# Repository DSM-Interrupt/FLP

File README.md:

# 구성

project FLP의 기기의 회로도, PCB, FW 코드 등이 담긴 파일입니다.
호스트 기기의 프레임 워크는 ESP-IDF를 이용하였고 Espressif ide를 이용하여서 CMAKE 형식의 프로젝트로 제작되었습니다.
터미널 기기의 프레임 워크는 STMCUBE를 이용하였습니다. 
host 기기의 같은경우 MCU는 ESP32-WROOM-32E를 이용하였으며 terminal기기의 경우 STM32F103C8T6을 사용하였습니다.

## 세부내용
### Hardware
- 433MHz 대역 통신을 위해 SX1278 모듈 기반의 안테나 매칭을 포함한 LoRa RF 공통 회로 설계
- MCP73831(Li-Po 충전) 및 AP2112K-3.3(LDO)을 사용하여 USB-C/배터리 입력을 받는 3.3V 전원 시스템 공통 회로 구성
- CP2104 USB-to-UART 브릿지 IC와 USB-C 커넥터를 사용한 PC 시리얼 통신 및 펌웨어 다운로드 공통 회로 구현
- L86-M33 GPS 모듈을 탑재하여 위치 정보 수집을 위한 공통 회로 및 안테나 인터페이스 설계
- Host(ESP32) 보드에 펌웨어의 효율적인 디버깅을 위한 JTAG 인터페이스 회로 추가 설계

### Firmware
- Host(ESP32) 펌웨어는 C 언어와 ESP-IDF(FreeRTOS)를 기반으로, Terminal(STM32F103) 펌웨어는 C 언어와 HAL 라이브러리를 기반으로 개발하여 LoRa 통신 시스템을 구축
- Terminal은 UART2로 GPS 모듈의 NMEA 센텐스를 파싱하며, 5초 주기 또는 '호출'/'위험' 버튼 입력 시 고유 ID, GPS 좌표, Target ID, 위험 상태를 "ID,Lat,Lon,TargetID,Danger" 형식의 문자열 패킷으로 LoRa 전송
- Host는 SPI를 통해 이 LoRa 패킷을 수신, split_lora_response 함수로 파싱하여 Target ID를 확인하고, TerminalDevice 구조체 배열로 관리되는 단말기 목록의 최신 GPS 좌표와 위험 상태를 갱신
- Host는 Wi-Fi(AP+STA 모드)로 인터넷에 연결하며, WSS 클라이언트를 통해 원격 서버로 모든 단말기 정보와 자체 GPS 수신 정보를 통합하여 주기적으로 JSON 전송
- Wi-Fi AP 모드에서 Captive Portal 기능을 포함한 웹 서버를 구동하여 사용자에게 Wi-Fi 연결 정보 및 AP 정보 설정 페이지를 제공하며, 이 설정값들과 등록된 단말기 ID 목록은 NVS에 영속 저장
- 특정 GPIO 버튼(CTRL + FIND_HOST) 조합을 통해 10초간 '단말기 등록 모드'로 진입하며, 이 동안 수신된 "REG,<ID>,<TARGET_ID>" 형식의 LoRa 등록 요청 패킷을 처리하여 새로운 단말기를 시스템에 추가하고 NVS에 저장

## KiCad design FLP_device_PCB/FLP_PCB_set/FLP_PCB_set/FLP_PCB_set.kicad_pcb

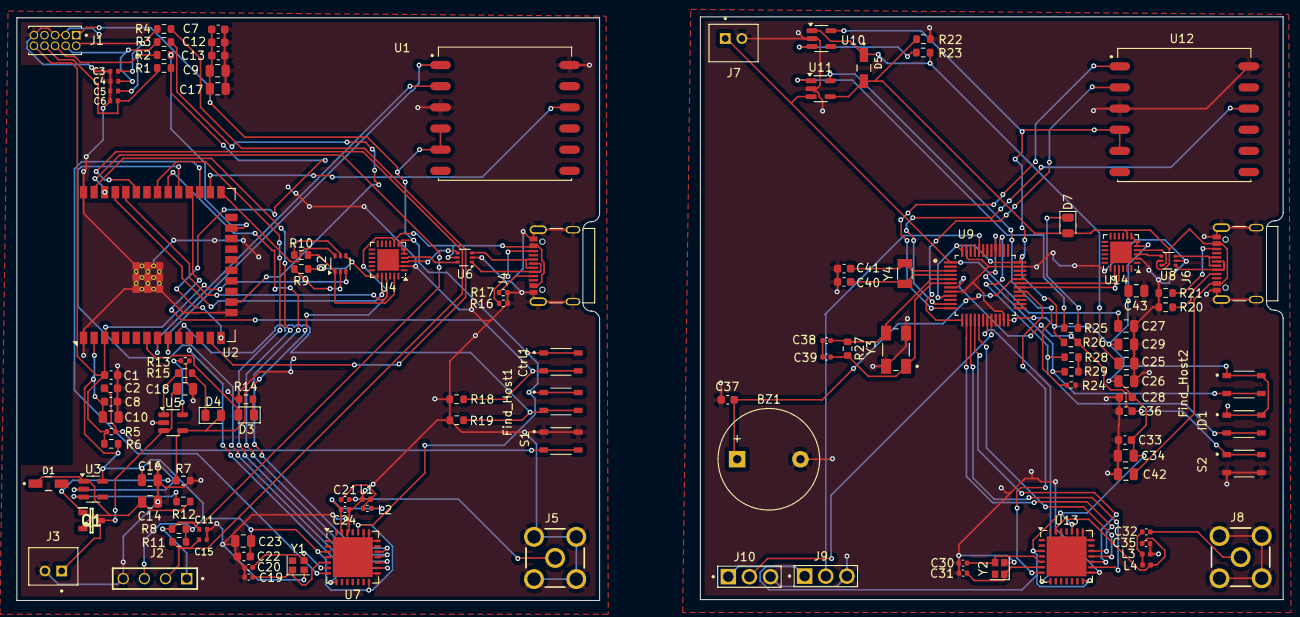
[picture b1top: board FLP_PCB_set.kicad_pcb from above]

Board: 2 copper layers, 152.1 x 70.1 mm, 118 parts (0 on the bottom side), 93 nets.

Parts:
BZ1: FQ 010; Buzzer_12x9.5RM7.6
C1, C7, C8, C28, C37: 1uF; C_0603_1608Metric
C2, C12, C22, C33, C36: 0.1uF; C_0603_1608Metric
C3, C4, C5, C6, C11, C15: PESD0402-140; RESC1005X35N
C9, C10, C14, C16, C18, C23, C25, C26, C27, C29, C34, C42: 22uF; C_0805_2012Metric
C13: 4.7uF; C_0603_1608Metric
C17, C43: 10uF; C_0805_2012Metric
C19, C20, C30, C31: 12pF; C_0402_1005Metric
C21, C32: 15pF; C_0402_1005Metric
C24, C35: 3.3pF; C_0402_1005Metric
C38, C39: 20pF; C_0402_1005Metric
C40, C41: 18pF; C_0603_1608Metric
Ctrl1: SKRPABE010; SW_SKRPABE010
D1, D5: MBR120VLSFT1G; DIOM3616X98N
D3, D4, D7: 150080GS75000; LED_0805_2012Metric
Find_Host1, Find_Host2: SKRPABE010; SW_SKRPABE010
ID1: SKRPABE010; SW_SKRPABE010
J1: GRPB052VWVN-RC; SULLINS_GRPB052VWVN-RC
J2: OLED; SAMTEC_HTSW-104-20-TM-S
J3, J7: B2B-PH-K-S; JST_B2B-PH-K-S
J4, J6: 12402012E212A; AMPHENOL_12402012E212A
J5, J8: SMA-J-P-X-ST-TH1; SAMTEC_SMA-J-P-X-ST-TH1
J9, J10: 61300311121; WURTH_61300311121
L1, L3: 47nH; L_0402_1005Metric
L2: 18nH; C_0402_1005Metric
L4: 18nH; L_0402_1005Metric
Q1: DMG3415UQ-7; SOT96P240X110-3N
Q2: UMH3N; SOT-363_SC-70-6
R1, R2, R3, R4: 100R; R_0603_1608Metric
R5: 22R; R_0402_1005Metric
R6, R9, R10, R18, R19, R26, R28, R29: 10K; R_0603_1608Metric
R7, R12, R22, R23: 100K; R_0603_1608Metric
R8, R11: 2.2K; R_0603_1608Metric
R13, R24: 2K; R_0402_1005Metric
R14, R15, R25: 1K; R_0603_1608Metric
R16, R17: 5.1K; R_0402_1005Metric
R20, R21: 5.1K; R_0603_1608Metric
R27: 1M; R_0603_1608Metric
S1, S2: SKRPABE010; SW_SKRPABE010
U1, U12: L86-M33; XCVR_L86-M33
U2: ESP32-WROOM-32E
U3, U10: AP2112K-3.3; SOT-23-5
U4, U14: CP2104; QFN-24-1EP_4x4mm_P0.5mm_EP2.6x2.6mm
U5, U11: MCP73831-2-OT; SOT-23-5
U6, U8: USBLC6-2P6; SOT-666
U7, U13: SX1278; QFN-28-1EP_6x6mm_P0.65mm_EP4.8x4.8mm
U9: STM32F103C8T6; QFP50P900X900X160-48N
Y1, Y2: 32MHz; Crystal_SMD_2016-4Pin_2.0x1.6mm
Y3: ABM3B-8.000MHZ-B2-T; XTAL_ABM3B-8.000MHZ-B2-T
Y4: 32.768kHz; Crystal_SMD_3215-2Pin_3.2x1.5mm

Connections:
/FLP_host/3.3V_OUT: C7.1, C8.1, C9.1, C10.1, C12.1, C13.1, C16.1, C17.1, C22.1, C23.2, Ctrl1.1, Ctrl1.2, Find_Host1.1, Find_Host1.2, J1.1, J2.03, R6.2, R8.2, R11.2, U1.4 (VCC), U1.5 (V_BCKP), U2.2 (VDD), U3.5 (VOUT), U4.5 (VIO), U4.6 (VDD), U4.7 (REGIN), U7.3 (VBAT_ANA), U7.14 (VBAT_DIG), U7.24 (VBAT_RF)
/FLP_host/5v_USB_OUT: D1.2, D4.2 (A), J4.A4_B9 (VBUS), J4.B4_A9 (VBUS), Q1.1 (G), R7.1, U4.8 (VBUS), U5.4 (V_{DD}), U6.5 (VBUS)
/FLP_host/Ctrl: Ctrl1.3, Ctrl1.4, R18.1, U2.28 (IO17)
/FLP_host/DIO0(IRQ): U2.11 (IO26), U7.8 (DIO0)
/FLP_host/DTR: Q2.1 (E1), R10.1, U4.23 (~DTR)
/FLP_host/Find_Host: Find_Host1.3, Find_Host1.4, R19.1, U2.10 (IO25)
/FLP_host/GPS_Reset: U1.10 (~RESET), U2.26 (IO4)
/FLP_host/GPS_Rx: U1.1 (RXD1), U2.9 (IO33)
/FLP_host/GPS_TX: U1.2 (TXD1), U2.8 (IO32)
/FLP_host/I2C_SCL: C11.1, J2.01, R8.1, U2.36 (IO22)
/FLP_host/I2C_SDL: C15.1, J2.02, R11.1, U2.33 (IO21)
/FLP_host/IO0: Q2.6 (C1), U2.25 (IO0)
/FLP_host/MISO: U2.31 (IO19), U7.17 (MISO)
/FLP_host/MOSI: U2.37 (IO23), U7.18 (MOSI)
/FLP_host/MTCK: R3.1, U2.16 (IO13)
/FLP_host/MTDI: R1.1, U2.14 (IO12)
/FLP_host/MTDO: R2.1, U2.23 (IO15)
/FLP_host/MTMS: R4.1, U2.13 (IO14)
/FLP_host/NSS(CS): U2.30 (IO18), U7.19 (NSS)
/FLP_host/RESET: U2.27 (IO16), U7.7 (~RESET)
/FLP_host/RTS: Q2.4 (E2), R9.1, U4.19 (~RTS)
/FLP_host/RX: U2.34 (RXD0/IO3), U4.21 (TXD)
/FLP_host/SCK: U2.29 (IO5), U7.16 (SCK)
/FLP_host/TEST LED: D3.2 (A), U2.7 (IO35)
/FLP_host/TX: U2.35 (TXD0/IO1), U4.20 (RXD)
/FLP_host/VBAT: C18.1, J3.1, Q1.3 (D), U5.3 (V_{BAT})
/FLP_terminal/BOOT_Mode/3.3V_in: C26.1, C28.1, C29.1, C33.1, C34.2, C43.1, Find_Host2.1, Find_Host2.2, ID1.1, ID1.2, J9.1, J10.1, R26.1, U9.9 (VDDA), U9.24 (VDD), U9.36 (VDD), U9.48 (VDD), U10.5 (VOUT), U12.4 (VCC), U12.5 (V_BCKP), U13.3 (VBAT_ANA), U13.14 (VBAT_DIG), U13.24 (VBAT_RF), U14.5 (VIO), U14.6 (VDD), U14.7 (REGIN)
/FLP_terminal/BOOT_Mode/BOOT0: J9.2, U9.44 (BOOT0)
/FLP_terminal/BOOT_Mode/BOOT1: J10.2, U9.20 (PB2)
/FLP_terminal/Bat/5v_USB_OUT: C42.2, D5.2, D7.2 (A), J6.A4_B9 (VBUS), J6.B4_A9 (VBUS), R22.1, U8.5 (VBUS), U11.4 (V_{DD}), U14.8 (VBUS)
/FLP_terminal/Bat/VBAT: C27.1, J7.1, U9.1 (VBAT), U11.3 (V_{BAT})
/FLP_terminal/GPS/GPS_Reset: U9.11 (PA1), U12.10 (~RESET)
/FLP_terminal/GPS/GPS_Rx: U9.12 (PA2), U12.1 (RXD1)
/FLP_terminal/GPS/GPS_TX: U9.13 (PA3), U12.2 (TXD1)
/FLP_terminal/LoRa/DIO0(IRQ): U9.19 (PB1), U13.8 (DIO0)
/FLP_terminal/LoRa/MISO: U9.16 (PA6), U13.17 (MISO)
/FLP_terminal/LoRa/MOSI: U9.17 (PA7), U13.18 (MOSI)
/FLP_terminal/LoRa/NSS(CS): U9.14 (PA4), U13.19 (NSS)
/FLP_terminal/LoRa/RESET: U9.29 (PA8), U13.7 (~RESET)
/FLP_terminal/LoRa/SCK: U9.15 (PA5), U13.16 (SCK)
/FLP_terminal/STM32/Buzzer: BZ1.1 (+), C37.1, U9.32 (PA11)
/FLP_terminal/STM32/Find_Host: Find_Host2.3, Find_Host2.4, R29.1, U9.40 (PB4)
/FLP_terminal/STM32/ID: ID1.3, ID1.4, R28.1, U9.39 (PB3)
/FLP_terminal/STM32/OSC_IN: C38.2, R27.1, U9.5 (PD0_OSC_IN), Y3.3
/FLP_terminal/STM32/OSC_OUT: C39.2, R27.2, U9.6 (PD1_OSC_OUT), Y3.1
/FLP_terminal/STM32/PC_OSC_IN: C41.1, U9.3 (PC14-OSC32_IN), Y4.1
/FLP_terminal/STM32/PC_OSC_OUT: C40.1, U9.4 (PC15-OSC32_OUT), Y4.2
/FLP_terminal/STM32/RX: U9.31 (PA10), U14.21 (TXD)
/FLP_terminal/STM32/TX: U9.30 (PA9), U14.20 (RXD)
/FLP_terminal/UART_USB/CC_1: J6.A5 (CC1), R20.1
/FLP_terminal/UART_USB/CC_2: J6.B5 (CC2), R21.1
/FLP_terminal/UART_USB/D+: U8.4 (I/O2), U14.3 (D+)
/FLP_terminal/UART_USB/D-: U8.6 (I/O1), U14.4 (D-)
EN: C1.1, J1.10, Q2.3 (C2), R5.2, R6.1, U2.3 (EN)
GND: BZ1.2 (-), C1.2, C2.1, C3.2, C4.1, C5.1, C6.2, C7.2, C8.2, C9.2, C10.2, C11.2, C12.2, C13.2, C14.2, C15.2, C16.2, C17.2, C18.2, C19.1, C20.1, C22.2, C23.1, C24.2, C25.2, C26.2, C27.2, C28.2, C29.2, C30.1, C31.1, C33.2, C34.1, C35.2, C36.1, C37.2, C40.2, C41.2, C42.1, C43.2, J1.3, J1.5, J1.9, J2.04, J3.2, J4.A1_B12 (GND), J4.B1_A12 (GND), J4.SH1 (SHIELD), J4.SH2 (SHIELD), J4.SH3 (SHIELD), J4.SH4 (SHIELD), J5.2, J5.3, J5.4, J5.5, J6.A1_B12 (GND), J6.B1_A12 (GND), J6.SH1 (SHIELD), J6.SH2 (SHIELD), J6.SH3 (SHIELD), J6.SH4 (SHIELD), J7.2, J8.2, J8.3, J8.4, J8.5, J9.3, J10.3, L1.1, L3.1, R7.2, R13.1, R14.2, R16.1, R17.1, R18.2, R19.2, R20.2, R21.2, R22.2, R24.1, R28.2, R29.2, S1.1, S1.2, S2.3, S2.4, U1.3 (GND), U1.12 (GND), U2.1 (GND), U2.15 (GND), U2.38 (GND), U2.39 (GND), U3.2 (GND), U4.2 (GND), U4.25 (GND), U5.2 (V_{SS}), U6.2 (GND), U7.15 (GND), U7.21 (GND), U7.22 (GND), U7.23 (GND), U7.26 (GND), U7.29 (GND), U8.2 (GND), U9.8 (VSSA), U9.23 (VSS), U9.35 (VSS), U9.47 (VSS), U10.2 (GND), U11.2 (V_{SS}), U12.3 (GND), U12.12 (GND), U13.15 (GND), U13.21 (GND), U13.22 (GND), U13.23 (GND), U13.26 (GND), U13.29 (GND), U14.2 (GND), U14.25 (GND), Y3.2 (GND), Y3.4 (GND)
unnamed: C2.2, R5.1, S1.3, S1.4
unnamed: C3.1, J1.2, R4.2
unnamed: C4.2, J1.4, R3.2
unnamed: C5.2, J1.6, R2.2
unnamed: C6.1, J1.8, R1.2
unnamed: C21.1, L1.2, L2.1
unnamed: C21.2, J5.1
unnamed: C32.1, L3.2, L4.1
unnamed: C32.2, J8.1
unnamed: C38.1, C39.1
unnamed: D3.1 (K), R14.1
unnamed: D4.1 (K), R15.2
unnamed: D7.1 (K), R25.2
unnamed: J4.A5 (CC1), R17.2
unnamed: J4.B5 (CC2), R16.2
unnamed: J4.A6 (D+), J4.B6 (D+), U6.3 (I/O2)
unnamed: J4.A7 (D-), J4.B7 (D-), U6.1 (I/O1)
unnamed: J6.A6 (D+), J6.B6 (D+), U8.3 (I/O2)
unnamed: J6.A7 (D-), J6.B7 (D-), U8.1 (I/O1)
unnamed: C14.1, D1.1, Q1.2 (S), R12.2, U3.1 (VIN)
unnamed: Q2.2 (B1), R9.2
unnamed: Q2.5 (B2), R10.2
unnamed: C25.1, D5.1, R23.2, U10.1 (VIN)
unnamed: R12.1, U3.3 (EN)
unnamed: U4.3 (D+), U6.4 (I/O2)
unnamed: U4.4 (D-), U6.6 (I/O1)
unnamed: R13.2, U5.5 (PROG)
unnamed: R15.1, U5.1 (STAT)
unnamed: C24.1, L2.2, U7.27 (PA_BOOST)
unnamed: C19.2, U7.5 (XTA), Y1.2
unnamed: C20.2, U7.6 (XTB), Y1.1
unnamed: C36.2, R26.2, S2.1, S2.2, U9.7 (NRST)
unnamed: R23.1, U10.3 (EN)
unnamed: R24.2, U11.5 (PROG)
unnamed: R25.1, U11.1 (STAT)
unnamed: C35.1, L4.2, U13.27 (PA_BOOST)
unnamed: C30.2, U13.5 (XTA), Y2.2
unnamed: C31.2, U13.6 (XTB), Y2.1

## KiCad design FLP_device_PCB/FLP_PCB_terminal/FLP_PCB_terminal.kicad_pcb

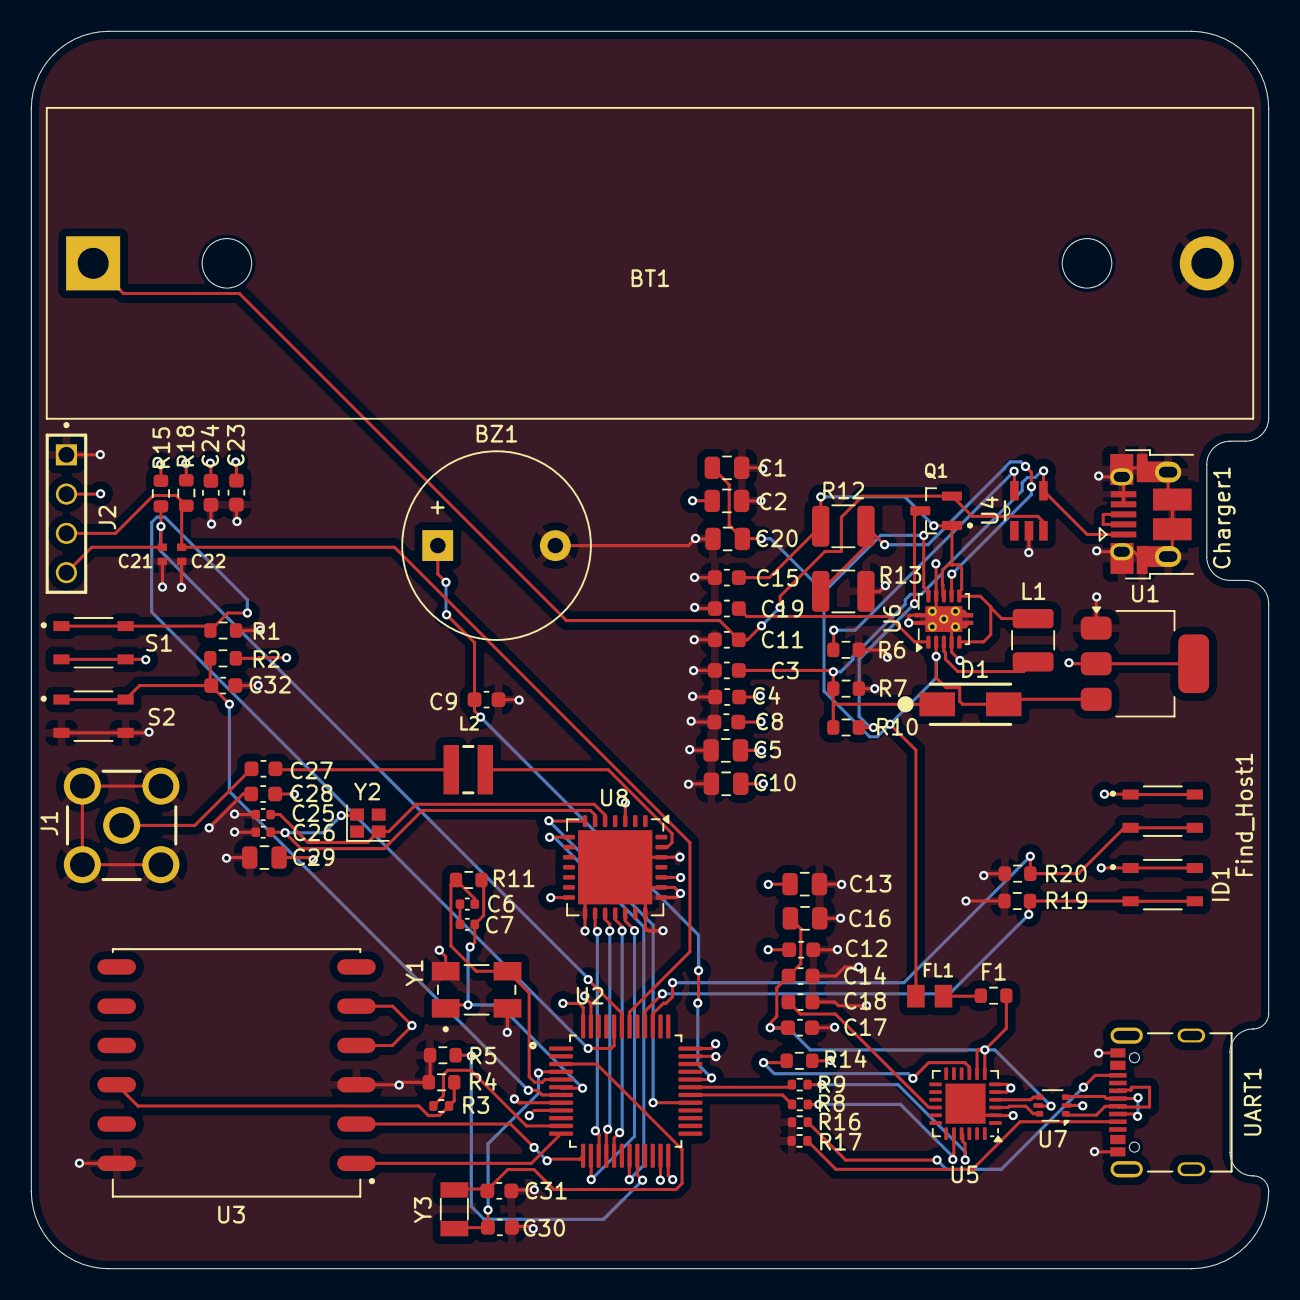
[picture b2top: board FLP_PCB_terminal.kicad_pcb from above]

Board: 4 copper layers, 80.0 x 80.0 mm, 79 parts (0 on the bottom side), 54 nets.

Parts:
BT1: Battery_Cell; BatteryHolder_MPD_BH-18650-PC2
BZ1: Buzzer; Buzzer_12x9.5RM7.6
C1, C2, C5, C10, C13, C16, C20, C29: 22uF; C_0805_2012Metric
C3, C11, C14, C15, C18, C23: 4.7uF; C_0603_1608Metric
C4, C8, C9, C19, C28: 1uF; C_0603_1608Metric
C6, C7: 20pF; C_0402_1005Metric
C12, C17, C24, C30, C31, C32: 0.1uF; C_0603_1608Metric
C21, C22: PESD0402-140; RESC1005X35N
C25, C26: 12pF; C_0402_1005Metric
C27: 2.2pF; C_0603_1608Metric
Charger1: Charger; USB_Micro-B_Amphenol_10103594-0001LF_Horizontal
D1: D_Schottky; DIOM5226X220N
F1: Polyfuse; R_0603_1608Metric
FL1: BLM21PG221SN1D; BEADC2012X105N
Find_Host1: SKRPABE010; SW_SKRPABE010
ID1: SKRPABE010; SW_SKRPABE010
J1: SMA-J-P-X-ST-TH1; SAMTEC_SMA-J-P-X-ST-TH1
J2: OLED; SAMTEC_HTSW-104-20-TM-S
L1: 2.2uH; L_1210_3225Metric
L2: WE-TPC_2811
Q1: Q_PMOS_DSG; SOT95P237X112-3N
R1, R2, R5, R6, R7, R14, R19, R20: 10K; R_0603_1608Metric
R3: 100R; R_0402_1005Metric
R4, R10: 1K; R_0603_1608Metric
R8, R9: 22R; R_0402_1005Metric
R11: 1M; R_0603_1608Metric
R12: 2M; R_1210_3225Metric
R13: 180K; R_1210_3225Metric
R15, R18: 2.2K; R_0603_1608Metric
R16, R17: 5.1K; R_0402_1005Metric
S1, S2: SKRPABE010; SW_SKRPABE010
U1: AMS1117-3.3; SOT-223-3_TabPin2
U2: STM32F103C8T6; QFP50P900X900X160-48N
U3: L86-M33; XCVR_L86-M33
U4: MCP73831-2-OT; SOT95P280X145-5N
U5: CP2104; QFN-24-1EP_4x4mm_P0.5mm_EP2.6x2.6mm
U6: TPS61200DRC; Texas_S-PVSON-N10_ThermalVias
U7: USBLC6-2P6; SOT-666
U8: SX1278; QFN-28-1EP_6x6mm_P0.65mm_EP4.8x4.8mm
UART1: USB_C_Receptacle_USB2.0_16P; AMPHENOL_12402012E212A
Y1: ABM3B-8.000MHZ-B2-T; XTAL_ABM3B-8.000MHZ-B2-T
Y2: 32MHz; Crystal_SMD_2016-4Pin_2.0x1.6mm
Y3: 32.768kHz; Crystal_SMD_3215-2Pin_3.2x1.5mm

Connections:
3.3V OUT: C2.1, C4.2, C5.2, C8.2, C10.2, C12.1, C13.2, C23.1, C24.1, C28.2, C29.2, Find_Host1.1, Find_Host1.2, ID1.1, ID1.2, J2.02, R2.1, R14.2, R15.2, R18.2, S1.3, S1.4, U1.2 (VO), U2.9 (VDDA), U2.24 (VDD), U2.36 (VDD), U2.48 (VDD), U3.4 (VCC), U3.5 (V_BCKP), U5.5 (VIO), U5.6 (VDD), U8.3 (VBAT_ANA), U8.14 (VBAT_DIG), U8.24 (VBAT_RF)
5v OUT: C1.1, C20.1, FL1.2, U1.3 (VI), U6.2 (VOUT), U6.10 (FB)
BOOT0: R1.2, S1.1, S1.2, U2.44 (BOOT0)
Buzzer: BZ1.1 (+), C9.1, U2.32 (PA11)
DIO0(IRQ): U2.19 (PB1), U8.8 (DIO0)
Find_Host: Find_Host1.3, Find_Host1.4, R20.2, U2.39 (PB3)
GND: BT1.2 (-), BZ1.2 (-), C1.2, C2.2, C3.2, C4.1, C5.1, C8.1, C9.2, C10.1, C11.2, C12.2, C13.1, C14.2, C15.2, C16.2, C17.1, C18.2, C19.2, C20.2, C21.2, C22.2, C23.2, C24.2, C25.1, C26.1, C28.1, C29.1, C30.2, C31.2, C32.1, Charger1.4 (ID), Charger1.5 (GND), Charger1.6 (Shield), J1.2, J1.3, J1.4, J1.5, J2.01, R1.1, R4.1, R5.1, R6.2, R7.2, R13.2, R16.1, R17.1, R19.1, R20.1, S2.3, S2.4, U1.1 (GND), U2.8 (VSSA), U2.23 (VSS), U2.35 (VSS), U2.47 (VSS), U3.3 (GND), U3.12 (GND), U4.2 (V_{SS}), U5.2 (GND), U5.25 (GND), U6.4 (PGND), U6.9 (GND), U6.11 (PAD), U7.2 (GND), U8.15 (GND), U8.21 (GND), U8.22 (GND), U8.23 (GND), U8.26 (GND), U8.29 (GND), Y1.2 (GND), Y1.4 (GND)
GPS_Reset: R3.1, U2.11 (PA1)
GPS_Rx: U2.12 (PA2), U3.1 (RXD1)
GPS_TX: U2.13 (PA3), U3.2 (TXD1)
I2C SCL: C22.1, J2.03, R18.1, U2.42 (PB6)
I2C SDL: C21.1, J2.04, R15.1, U2.43 (PB7)
ID: ID1.3, ID1.4, R19.2, U2.40 (PB4)
MISO: U2.16 (PA6), U8.17 (MISO)
MOSI: U2.17 (PA7), U8.18 (MOSI)
NRST: C32.2, R2.2, S2.1, S2.2, U2.7 (NRST)
NSS(CS): U2.14 (PA4), U8.19 (NSS)
unnamed: BT1.1 (+), C11.1, Q1.2 (S), U4.3 (V_{BAT})
unnamed: C6.1, C7.1
unnamed: C27.1, J1.1
unnamed: C27.2, L2.1
unnamed: Charger1.2 (D-), Charger1.3 (D+)
unnamed: C3.1, Charger1.1 (VBUS), R7.1, R10.1, U4.4 (V_{DD})
unnamed: F1.2, FL1.1
unnamed: C15.1, L1.1, Q1.1 (D), R12.1, U6.5 (VIN), U6.6 (EN), U6.8 (PS)
unnamed: Q1.3 (G), R10.2
unnamed: R5.2, U2.20 (PB2)
unnamed: R3.2, R4.2, U3.10 (~RESET)
unnamed: R6.1, U4.5 (PROG)
unnamed: U5.3 (D+), U7.6 (I/O1)
unnamed: U5.4 (D-), U7.4 (I/O2)
unnamed: C14.1, C16.1, C17.2, F1.1, U5.7 (REGIN), U5.8 (VBUS), U7.5 (VBUS)
unnamed: R8.2, U5.20 (RXD)
unnamed: R9.2, U5.21 (TXD)
unnamed: C18.1, U5.16 (VPP)
unnamed: R14.1, U5.9 (~RST)
unnamed: L1.2, U6.3 (L)
unnamed: R12.2, R13.1, U6.7 (UVLO)
unnamed: C19.1, U6.1 (VAUX)
unnamed: U7.1 (I/O1), UART1.A6 (D+), UART1.B6 (D+)
unnamed: U7.3 (I/O2), UART1.A7 (D-), UART1.B7 (D-)
unnamed: L2.2, U8.27 (PA_BOOST)
unnamed: C25.2, U8.5 (XTA), Y2.2
unnamed: C26.2, U8.6 (XTB), Y2.1
unnamed: R17.2, UART1.A5 (CC1)
unnamed: R16.2, UART1.B5 (CC2)
OSC_IN: C6.2, R11.1, U2.5 (PD0_OSC_IN), Y1.3
OSC_OUT: C7.2, R11.2, U2.6 (PD1_OSC_OUT), Y1.1
PC_OSC_IN: C31.1, U2.3 (PC14-OSC32_IN), Y3.1
PC_OSC_OUT: C30.1, U2.4 (PC15-OSC32_OUT), Y3.2
RESET: U2.29 (PA8), U8.7 (~RESET)
RX: R9.1, U2.31 (PA10)
SCK: U2.15 (PA5), U8.16 (SCK)
TX: R8.1, U2.30 (PA9)

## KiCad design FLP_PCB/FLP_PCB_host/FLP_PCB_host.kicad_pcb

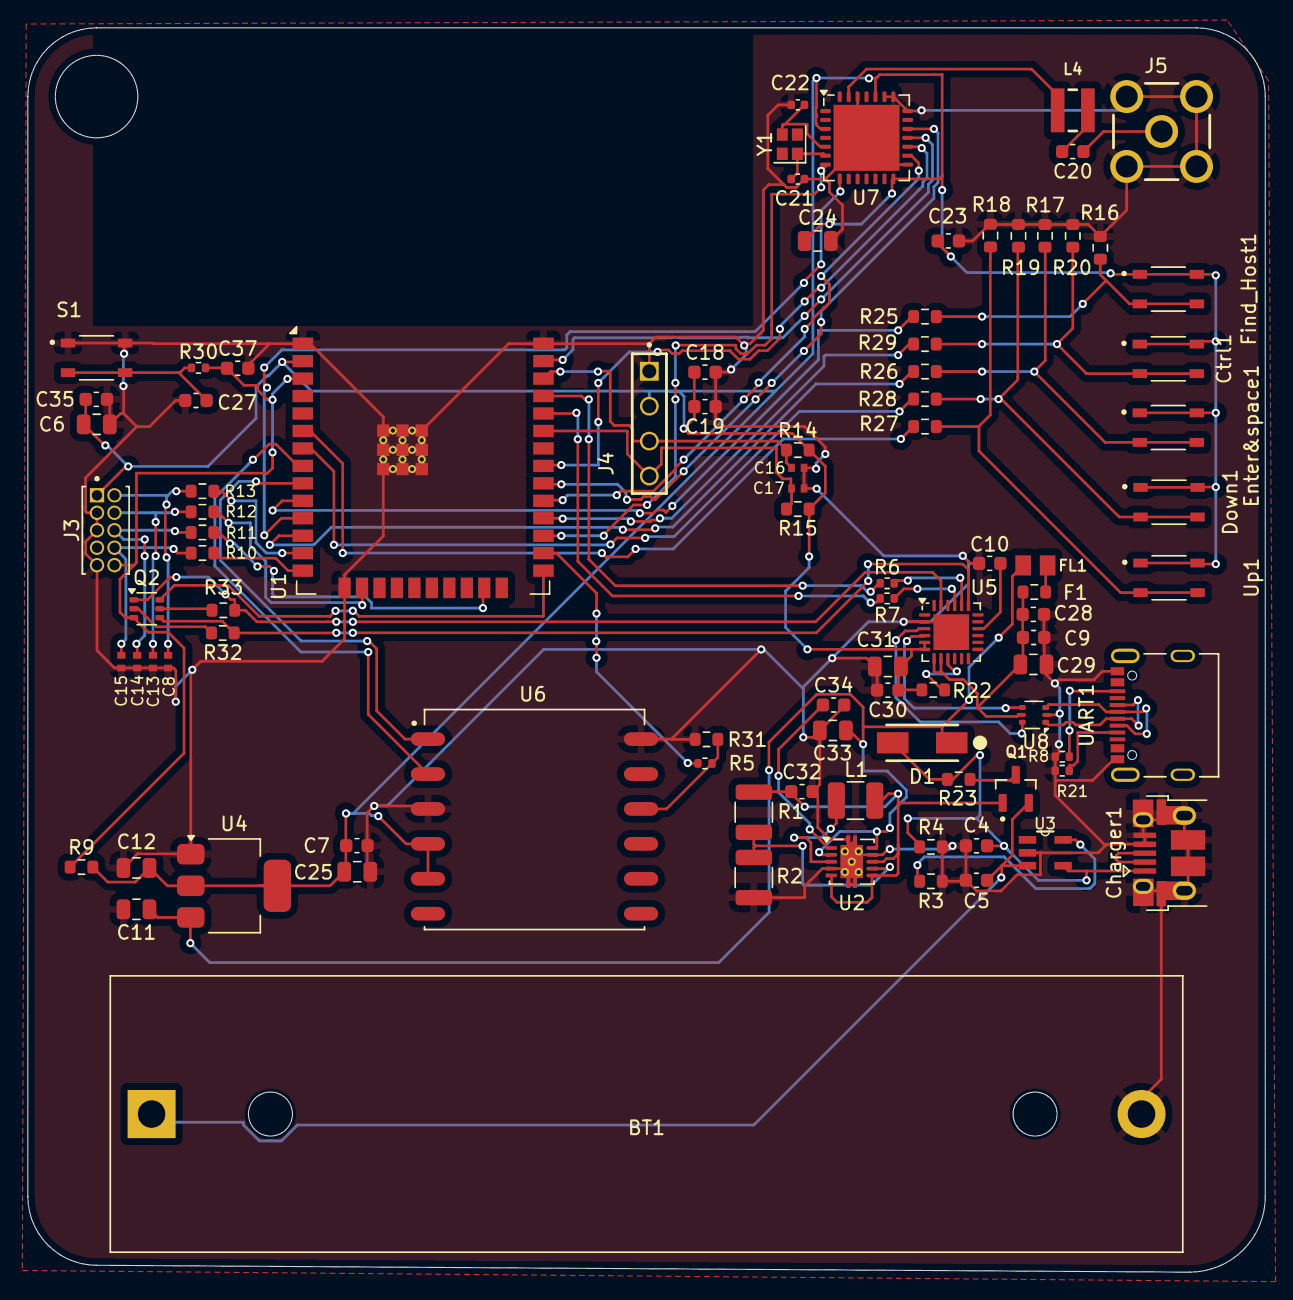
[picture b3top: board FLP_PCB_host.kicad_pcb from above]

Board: 2 copper layers, 90.0 x 90.5 mm, 92 parts (0 on the bottom side), 68 nets.

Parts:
BT1: Battery_Cell; BatteryHolder_MPD_BH-18650-PC2
C4, C5, C9, C10, C19, C32: 4.7uF; C_0603_1608Metric
C6, C11, C12, C24, C25, C29, C31, C33: 22uF; C_0805_2012Metric
C7, C34, C35, C37: 1uF; C_0603_1608Metric
C8, C13, C14, C15, C16, C17: PESD0402-140; RESC1005X35N
C18, C23, C27, C28, C30: 0.1uF; C_0603_1608Metric
C20: 27pF; C_0603_1608Metric
C21, C22: 12pF; C_0402_1005Metric
Charger1: 10103594-0001LF; USB_Micro-B_Amphenol_10103594-0001LF_Horizontal
Ctrl1: SKRPABE010; SW_SKRPABE010
D1: MBRA160T3G; DIOM5226X220N
Down1: SKRPABE010; SW_SKRPABE010
Enter&space1: SKRPABE010; SW_SKRPABE010
F1: 0603L100SLYR; R_0603_1608Metric
FL1: BLM21PG221SN1D; BEADC2012X105N
Find_Host1: SKRPABE010; SW_SKRPABE010
J3: GRPB052VWVN-RC; SULLINS_GRPB052VWVN-RC
J4: OLED; SAMTEC_HTSW-104-20-TM-S
J5: SMA-J-P-X-ST-TH1; SAMTEC_SMA-J-P-X-ST-TH1
L1: 2.2uH; L_1210_3225Metric
L4: 744028000056; WE-TPC_2811
Q1: Q_PMOS_DSG; SOT95P237X112-3N
Q2: UMH3N; SOT-363_SC-70-6
R1: 2M; R_1210_3225Metric
R2: 180K; R_1210_3225Metric
R3, R4, R9, R16, R17, R18, R19, R20, R22, R32, R33: 10K; R_0603_1608Metric
R5: 100R; R_0402_1005Metric
R6, R7, R30: 22R; R_0402_1005Metric
R8, R21: 5.1K; R_0402_1005Metric
R10, R11, R12, R13, R25, R26, R27, R28, R29: 100R; R_0603_1608Metric
R14, R15: 2.2K; R_0603_1608Metric
R23, R31: 1K; R_0603_1608Metric
S1: SKRPABE010; SW_SKRPABE010
U1: ESP32-WROOM-32E
U2: TPS61200DRC; Texas_S-PVSON-N10_ThermalVias
U3: MCP73831-2-OT; SOT95P280X145-5N
U4: AMS1117-3.3; SOT-223-3_TabPin2
U5: CP2104; QFN-24-1EP_4x4mm_P0.5mm_EP2.6x2.6mm
U6: L86-M33; XCVR_L86-M33
U7: SX1278; QFN-28-1EP_6x6mm_P0.65mm_EP4.8x4.8mm
U8: USBLC6-2P6; SOT-666
UART1: 12402012E212A; AMPHENOL_12402012E212A
Up1: SKRPABE010; SW_SKRPABE010
Y1: 32MHz; Crystal_SMD_2016-4Pin_2.0x1.6mm

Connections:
3.3V OUT: C6.1, C7.1, C12.1, C18.1, C19.1, C23.1, C24.2, C25.1, C30.1, C31.2, C35.1, Ctrl1.1, Ctrl1.2, Down1.1, Down1.2, Enter&space1.1, Enter&space1.2, Find_Host1.1, Find_Host1.2, J3.1, J4.02, R9.2, R14.2, R15.2, R22.2, U1.2 (VDD), U4.2 (VO), U5.5 (VIO), U5.6 (VDD), U6.4 (VCC), U6.5 (V_BCKP), U7.3 (VBAT_ANA), U7.14 (VBAT_DIG), U7.24 (VBAT_RF), Up1.1, Up1.2
5v OUT: C11.1, C33.1, FL1.2, U2.2 (VOUT), U2.10 (FB), U4.3 (VI)
Ctrl: R29.2, U1.28 (IO17)
DIO0(IRQ): U1.11 (IO26), U7.8 (DIO0)
DTR: Q2.1 (E1), R33.1, U5.23 (~DTR)
Down: R28.2, U1.7 (IO35)
EN: C37.1, J3.10, Q2.3 (C2), R9.1, R30.2, U1.3 (EN)
Enter&space: R26.2, U1.12 (IO27)
Find_Host: R25.2, U1.10 (IO25)
GND: BT1.2 (-), C4.2, C5.2, C6.2, C7.2, C8.2, C9.2, C10.2, C11.2, C12.2, C13.2, C14.2, C15.2, C16.2, C17.2, C18.2, C19.2, C21.1, C22.1, C23.2, C24.1, C25.2, C27.1, C28.1, C29.2, C30.2, C31.1, C32.2, C33.2, C34.2, C35.2, C37.2, Charger1.4 (ID), Charger1.5 (GND), Charger1.6 (Shield), J3.3, J3.5, J3.9, J4.01, J5.2, J5.3, J5.4, J5.5, R2.2, R3.2, R4.2, R8.1, R16.2, R17.2, R18.2, R19.2, R20.2, R21.1, R31.1, S1.1, S1.2, U1.1 (GND), U1.15 (GND), U1.38 (GND), U1.39 (GND), U2.4 (PGND), U2.9 (GND), U2.11 (PAD), U3.2 (V_{SS}), U4.1 (GND), U5.2 (GND), U5.25 (GND), U6.3 (GND), U6.12 (GND), U7.15 (GND), U7.21 (GND), U7.22 (GND), U7.23 (GND), U7.26 (GND), U7.29 (GND), U8.2 (GND)
GPS_Reset: R5.1, U1.26 (IO4)
GPS_Rx: U1.9 (IO33), U6.1 (RXD1)
GPS_TX: U1.8 (IO32), U6.2 (TXD1)
I2C SCL: C16.1, J4.03, R14.1, U1.36 (IO22)
I2C SDL: C17.1, J4.04, R15.1, U1.33 (IO21)
IO0: Q2.6 (C1), U1.25 (IO0)
MISO: U1.31 (IO19), U7.17 (MISO)
MOSI: U1.37 (IO23), U7.18 (MOSI)
MTCK: R12.1, U1.16 (IO13)
MTDI: R10.1, U1.14 (IO12)
MTDO: R11.1, U1.23 (IO15)
MTMS: R13.1, U1.13 (IO14)
NSS(CS): U1.30 (IO18), U7.19 (NSS)
unnamed: BT1.1 (+), C5.1, Q1.2 (S), U3.3 (V_{BAT})
unnamed: C8.1, J3.2, R13.2
unnamed: C13.1, J3.4, R12.2
unnamed: C14.1, J3.6, R11.2
unnamed: C15.1, J3.8, R10.2
unnamed: C20.1, J5.1
unnamed: C20.2, L4.1
unnamed: C27.2, R30.1, S1.3, S1.4
unnamed: Charger1.2 (D-), Charger1.3 (D+)
unnamed: C4.1, Charger1.1 (VBUS), R4.1, R23.1, U3.4 (V_{DD})
unnamed: Ctrl1.3, Ctrl1.4, R20.1, R29.1
unnamed: Down1.3, Down1.4, R19.1, R28.1
unnamed: Enter&space1.3, Enter&space1.4, R17.1, R26.1
unnamed: F1.2, FL1.1
unnamed: Find_Host1.3, Find_Host1.4, R16.1, R25.1
unnamed: C32.1, L1.1, Q1.1 (D), R1.1, U2.5 (VIN), U2.6 (EN), U2.8 (PS)
unnamed: Q1.3 (G), R23.2
unnamed: Q2.2 (B1), R32.2
unnamed: Q2.5 (B2), R33.2
unnamed: R18.1, R27.1, Up1.3, Up1.4
unnamed: L1.2, U2.3 (L)
unnamed: R1.2, R2.1, U2.7 (UVLO)
unnamed: C34.1, U2.1 (VAUX)
unnamed: R3.1, U3.5 (PROG)
unnamed: U5.3 (D+), U8.6 (I/O1)
unnamed: U5.4 (D-), U8.4 (I/O2)
unnamed: C9.1, C28.2, C29.1, F1.1, U5.7 (REGIN), U5.8 (VBUS), U8.5 (VBUS)
unnamed: R6.2, U5.20 (RXD)
unnamed: R7.2, U5.21 (TXD)
unnamed: C10.1, U5.16 (VPP)
unnamed: R22.1, U5.9 (~RST)
unnamed: R5.2, R31.2, U6.10 (~RESET)
unnamed: L4.2, U7.27 (PA_BOOST)
unnamed: C22.2, U7.5 (XTA), Y1.3
unnamed: C21.2, U7.6 (XTB), Y1.1
unnamed: U8.1 (I/O1), UART1.A6 (D+), UART1.B6 (D+)
unnamed: U8.3 (I/O2), UART1.A7 (D-), UART1.B7 (D-)
unnamed: R21.2, UART1.A5 (CC1)
unnamed: R8.2, UART1.B5 (CC2)
RESET: U1.27 (IO16), U7.7 (~RESET)
RTS: Q2.4 (E2), R32.1, U5.19 (~RTS)
RX: R7.1, U1.34 (RXD0/IO3)
SCK: U1.29 (IO5), U7.16 (SCK)
TX: R6.1, U1.35 (TXD0/IO1)
Up: R27.2, U1.6 (IO34)

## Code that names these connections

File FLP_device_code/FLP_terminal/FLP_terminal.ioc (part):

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Mcu.Name=STM32F103C(8-B)Tx
Mcu.Package=LQFP48
Mcu.UserName=STM32F103C8Tx
PA11.GPIOParameters=GPIO_Label
PA11.GPIO_Label=buzzer
PA11.Signal=GPIO_Output
PA2.GPIOParameters=GPIO_Label
PA2.GPIO_Label=GPS_Rx
PA2.Mode=Asynchronous
PA2.Signal=USART2_TX
PA3.GPIOParameters=GPIO_Label
PA3.GPIO_Label=GPS_Tx
PA3.Mode=Asynchronous
PA3.Signal=USART2_RX
PA4.GPIOParameters=GPIO_Label
PA4.GPIO_Label=SX1278_NSS
PA4.Signal=GPIO_Output
PA5.GPIOParameters=GPIO_Label
PA5.GPIO_Label=SX1278_SCK
PA5.Mode=Full_Duplex_Master
PA5.Signal=SPI1_SCK
PA6.GPIOParameters=GPIO_Label
PA6.GPIO_Label=SX1278_MISO
PA6.Mode=Full_Duplex_Master
PA6.Signal=SPI1_MISO
PA7.GPIOParameters=GPIO_Label
PA7.GPIO_Label=SX1278_MOSI
PA7.Mode=Full_Duplex_Master
PA7.Signal=SPI1_MOSI
PB1.GPIOParameters=GPIO_Label
PB1.GPIO_Label=DIO0
PB1.Signal=GPXTI1
PB3.GPIOParameters=GPIO_Label
PB3.GPIO_Label=find_host
PB3.Signal=GPIO_Input
PB4.GPIOParameters=GPIO_Label
PB4.GPIO_Label=ID
PB4.Signal=GPIO_Output
PB8.GPIOParameters=GPIO_Label
PB8.GPIO_Label=SX1278_RESET
PB8.Signal=GPIO_Output
RCC.SYSCLKFreq_VALUE=36000000
RCC.SYSCLKSource=RCC_SYSCLKSOURCE_PLLCLK
board=custom

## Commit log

2025-03-17 PCB update
2025-03-30 PCB first chack
2025-03-30 PCB first chack end
2025-03-30 PCB add GND plain
2025-03-30 PCB last add GND plain
2025-04-04 SCH update, PCB reset
2025-04-05 SCH finish PCB writing
2025-04-06 PCB writing
2025-04-08 host PCB and SCH finish
2025-04-13 terminal SCH
2025-04-15 modify terminal SCH
2025-04-18 host PCB and SCH bug fix
2025-04-23 modify
2025-04-23 host code
2025-04-24 host code modify
2025-04-28 host code modify & host PCB and SCH modify
2025-05-05 PCB and code modify
2025-05-06 code modify
2025-05-14 name fix and grb file add
2025-05-16 dir name change, host PCB finish
2025-06-03 PCB finish
2025-06-11 code adding
2025-06-12 code add
2025-06-12 code fix
2025-06-16 web fix
2025-06-18 bug fix
2025-06-19 PCB build up -> nomal modify
2025-06-19 WSS fix and Post fix and Optimization
2025-06-19 FLP_terminal code generation
2025-06-19 edit terminal
2025-06-21 rename folder name and terminal define function
2025-06-22 terminal define function and code add
2025-06-23 device_code Refactoring
2025-07-07 device_code fix and device_PCB fix
2025-09-13 new PCB adding
2025-09-18 FLP_set add
2025-09-29 PCB fixing end adding description pdf
2025-10-05 code refactoring
2025-10-07 PCB pdf add
2026-05-02 fgdsfsfdffsfs
